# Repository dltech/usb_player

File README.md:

# usb_player
simple USB SD mp3 player based on stm32 MCU\
TODO:\
schematic (OK)\
board\
register defs (OK)\
RCC (OK)\
I2S PCM1754 sound out\
lm4811 power regul (OK)\
ADC sound in\
SDIO\
FAT32\
MP3 decoder\
SPI\
CC1101 4FSK\
speex build\
OTG FS USB FLASH (sd adapter)\
OTG FS USB FLASH FAT32 HOST\
STM32 DAC sound output

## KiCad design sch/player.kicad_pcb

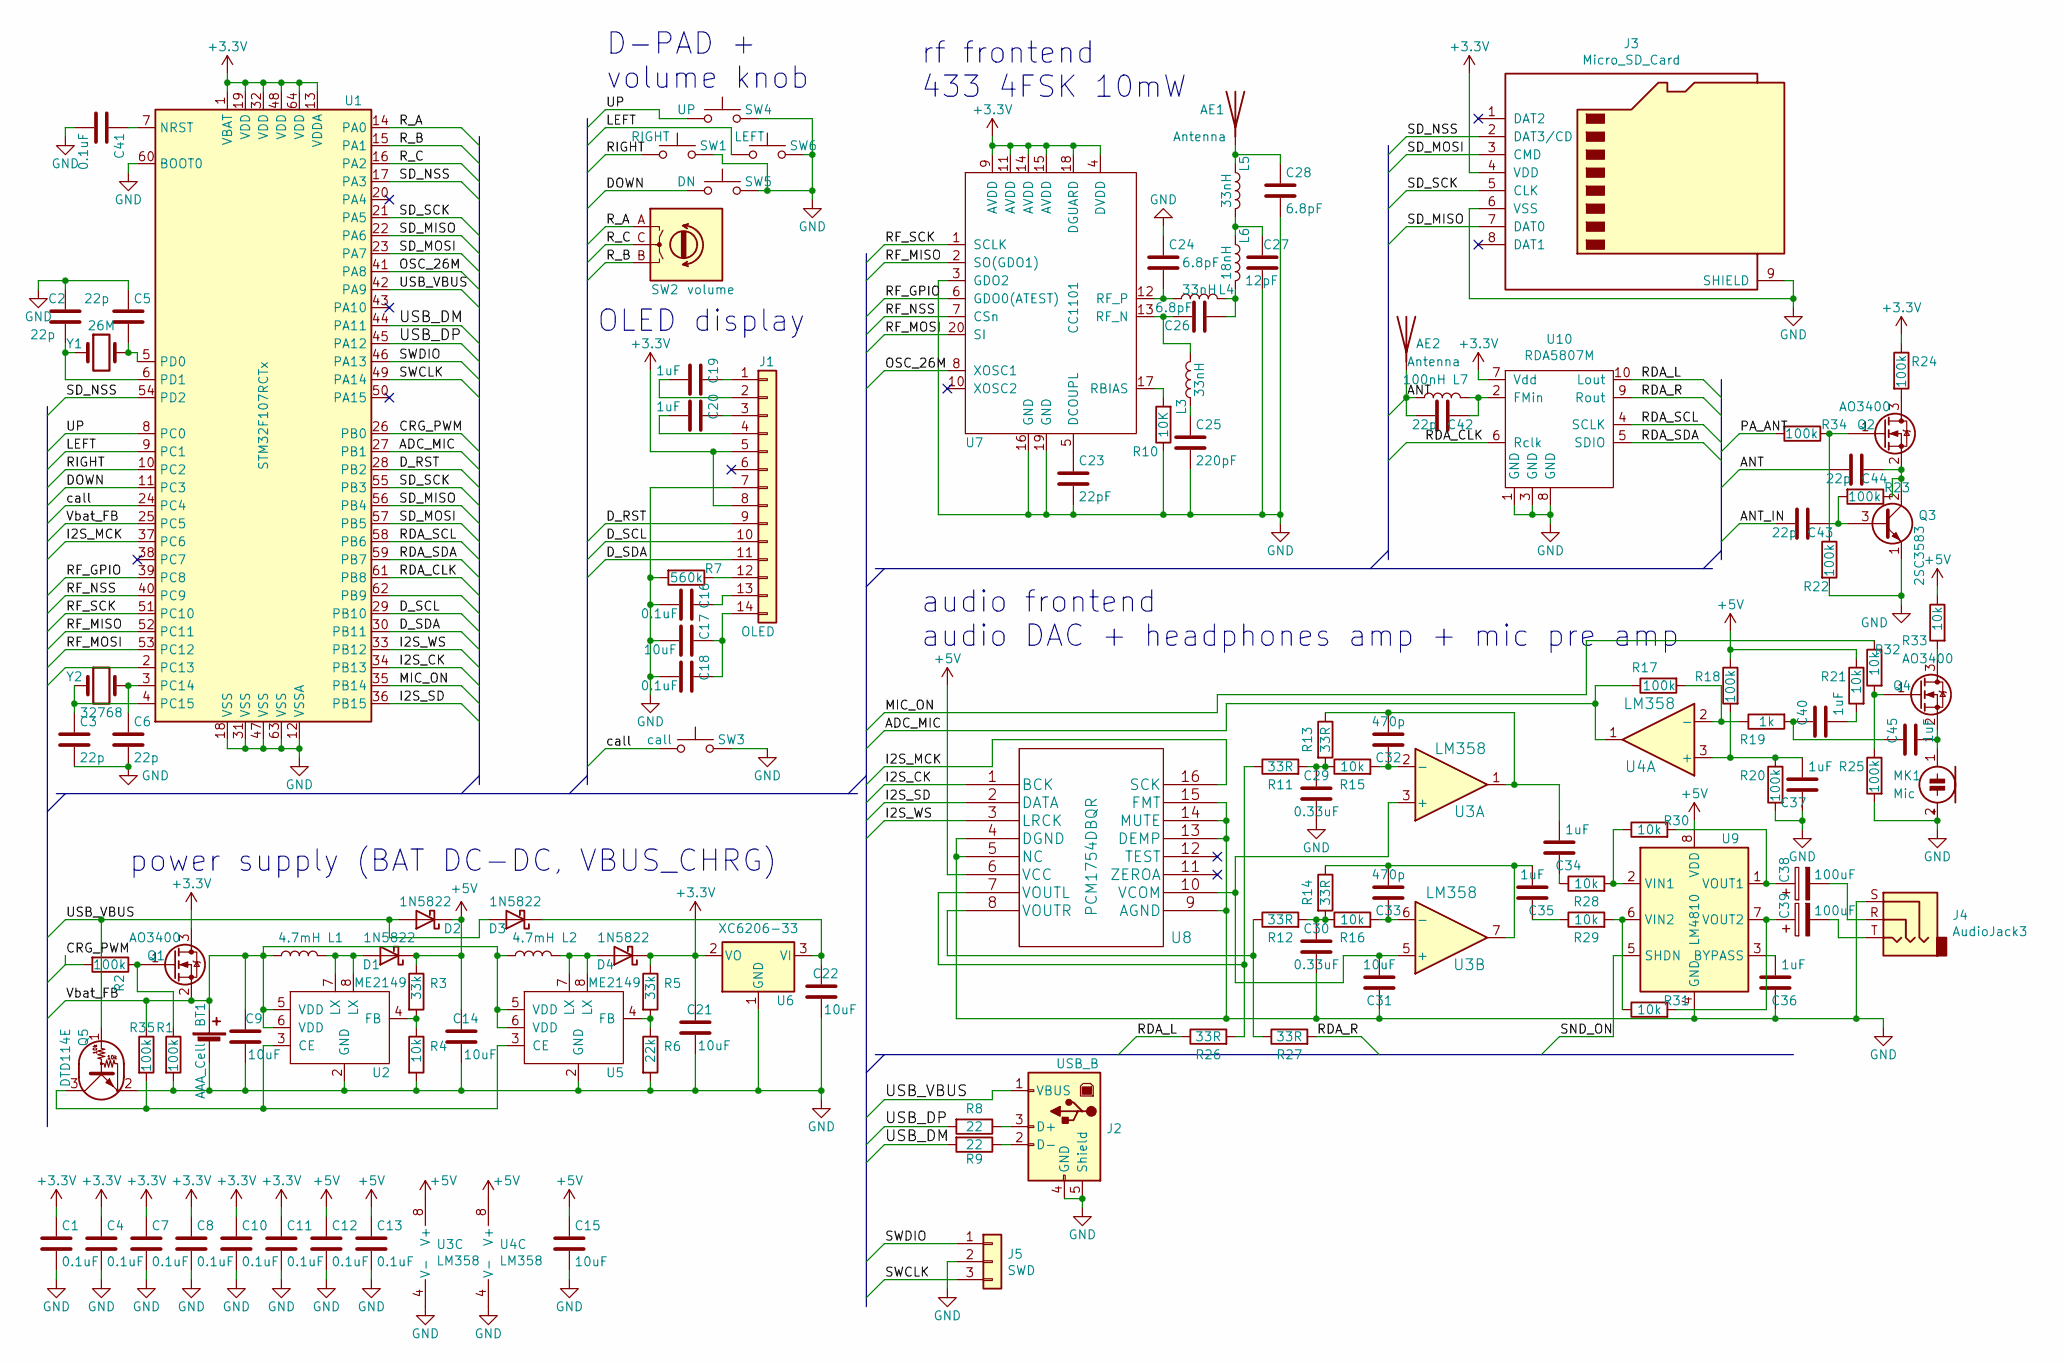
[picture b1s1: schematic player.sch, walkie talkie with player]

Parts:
AE1, AE2: Antenna; SolderWirePad_1x01_SMD_1x2mm
BT1: AAA_Cell; PinHeader_2x01_P2.54mm_Vertical
C1, C4, C7, C8, C10, C11, C12, C13, C16, C18, C41: 0.1uF; C_0402_1005Metric
C2, C3, C5, C6, C42, C43, C44: 22p; C_0402_1005Metric
C9, C14, C15, C17, C21, C22, C31: 10uF; C_0805_2012Metric
C19, C20, C34, C35, C36, C37, C40, C45: 1uF; C_0805_2012Metric
C23: 22pF; C_0402_1005Metric
C24, C26, C28: 6.8pF; C_0603_1608Metric
C25: 220pF; C_0603_1608Metric
C27: 12pF; C_0603_1608Metric
C29, C30: 0.33uF; C_0603_1608Metric
C32, C33: 470p; C_0603_1608Metric
C38, C39: 100uF; C_1206_3216Metric
D1, D2, D3, D4: 1N5822; D_SMA
J1: OLED; display_14p
J2: USB_B; USB_Micro-B_Molex_47346-0001
J3: Micro_SD_Card; microSD_HC_Hirose_DM3BT-DSF-PEJS
J4: AudioJack3; uefang
J5: SWD; 3WIRE_PADS
L1: 4.7mH; L_7.3x7.3_H4.5
L2: 4.7mH; L_1206_3216Metric
L3, L4, L5: 33nH; L_0603_1608Metric
L6: 18nH; L_0603_1608Metric
L7: 100nH; L_0603_1608Metric
MK1: Mic; CP_Radial_D5.0mm_P2.50mm
Q1, Q2, Q4: AO3400; SOT-23
Q3: 2SC3583; SOT-23
Q5: DTD114E; SOT-23
R1, R2, R20, R22, R23, R24, R25, R34, R35: 100k; R_0402_1005Metric
R3, R5: 33k; R_0805_2012Metric
R4, R15, R16, R21, R28, R29, R30, R31, R32, R33: 10k; R_0402_1005Metric
R6: 22k; R_0805_2012Metric
R7: 560k; R_0805_2012Metric
R8, R9: 22; R_0402_1005Metric
R10: 10K; R_0402_1005Metric
R11, R12, R13, R14, R26, R27: 33R; R_0402_1005Metric
R17, R18: 100k; C_0402_1005Metric
R19: 1k; R_0805_2012Metric
SW1: RIGHT; SW_PUSH_6mm
SW2: volume; mouse_encoder
SW3: call; SW_PUSH_6mm
SW4: UP; SW_PUSH_6mm
SW5: DN; SW_PUSH_6mm
SW6: LEFT; SW_PUSH_6mm
U1: STM32F107RCTx; LQFP-64_10x10mm_P0.5mm
U2, U5: ME2149; SSOP-8_3.9x5.05mm_P1.27mm
U3, U4: LM358; SSOP-8_3.9x5.05mm_P1.27mm
U6: XC6206-33; SOT-23
U7: CC1101; cc1101
U8: PCM1754DBQR; SSOP-16_3.9x4.9mm_P0.635mm
U9: LM4810; TSSOP-8_3x3mm_P0.65mm
U10: RDA5807M; MSOP-10_3x3mm_P0.5mm
Y1: 26M; Crystal_SMD_5032-2Pin_5.0x3.2mm
Y2: 32768; Crystal_SMD_2012-2Pin_2.0x1.2mm

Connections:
+5V: C12.1, C13.1, C14.2, C15.1, D1.1 (K), D2.1 (K), R3.1, R18.1, R21.1, R33.1, U3.8 (V+), U4.8 (V+), U8.6 (VCC), U9.8 (VDD)
/ADC_MIC: R17.1, U1.27 (PB1), U4.1
/ANT: AE2.1, C42.1, C44.1, L7.1
/ANT_IN: C43.1
/CRG_PWM: R2.2, U1.26 (PB0)
/DOWN: SW5.1, U1.11 (PC3)
/D_RST: J1.9, U1.28 (PB2)
/D_SCL: J1.10, U1.29 (PB10)
/D_SDA: J1.11, U1.30 (PB11)
/I2S_CK: U1.34 (PB13), U8.1 (BCK)
/I2S_MCK: U1.37 (PC6), U8.16 (SCK)
/I2S_SD: U1.36 (PB15), U8.2 (DATA)
/I2S_WS: U1.33 (PB12), U8.3 (LRCK)
/LEFT: SW6.1, U1.9 (PC1)
/MIC_ON: R32.1, U1.35 (PB14)
/OSC_26M: U1.41 (PA8), U7.8 (XOSC1)
/PA_ANT: R34.2
/RDA_CLK: U1.61 (PB8), U10.6 (Rclk)
/RDA_L: R26.1, U10.10 (Lout)
/RDA_R: R27.2, U10.9 (Rout)
/RDA_SCL: U1.58 (PB6), U10.4 (SCLK)
/RDA_SDA: U1.59 (PB7), U10.5 (SDIO)
/RF_GPIO: U1.39 (PC8), U7.6 (GDO0(ATEST))
/RF_MISO: U1.52 (PC11), U7.2 (SO(GDO1))
/RF_MOSI: U1.53 (PC12), U7.20 (SI)
/RF_NSS: U1.40 (PC9), U7.7 (CSn)
/RF_SCK: U1.51 (PC10), U7.1 (SCLK)
/RIGHT: SW1.1, U1.10 (PC2)
/R_A: SW2.A, U1.14 (PA0)
/R_B: SW2.B, U1.15 (PA1)
/R_C: SW2.C, U1.16 (PA2)
/SD_MISO: J3.7 (DAT0), U1.22 (PA6), U1.56 (PB4)
/SD_MOSI: J3.3 (CMD), U1.23 (PA7), U1.57 (PB5)
/SD_NSS: J3.2 (DAT3/CD), U1.17 (PA3), U1.54 (PD2)
/SD_SCK: J3.5 (CLK), U1.21 (PA5), U1.55 (PB3)
/SND_ON: U9.5 (SHDN)
/SWCLK: J5.3, U1.49 (PA14)
/SWDIO: J5.1, U1.46 (PA13)
/UP: SW4.1, U1.8 (PC0)
/USB_DM: R9.2, U1.44 (PA11)
/USB_DP: R8.2, U1.45 (PA12)
/USB_VBUS: D2.2 (A), D3.2 (A), J2.1 (VBUS), Q5.1 (B), U1.42 (PA9)
/Vbat_FB: BT1.1 (+), C9.2, L1.1, L2.1, Q1.2 (S), R35.1, U1.25 (PC5), U2.5 (VDD), U2.6 (VDD), U5.5 (VDD), U5.6 (VDD)
/call: SW3.1, U1.24 (PC4)
GND: BT1.2 (-), C1.2, C2.1, C3.2, C4.2, C5.1, C6.2, C7.2, C8.2, C9.1, C10.2, C11.2, C12.2, C13.2, C14.1, C15.2, C16.2, C17.1, C18.2, C21.1, C22.1, C23.2, C24.1, C25.2, C27.2, C28.2, C29.1, C30.1, C31.1, C36.1, C37.1, C41.2, J1.7, J2.4 (GND), J2.5 (Shield), J3.6 (VSS), J3.9 (SHIELD), J4.S, J5.2, MK1.2 (+), Q3.1 (E), Q5.2 (E), R1.2, R4.2, R6.2, R7.2, R10.1, R20.2, R22.2, R25.2, SW1.2, SW3.2, SW4.2, SW5.2, SW6.2, U1.12 (VSSA), U1.18 (VSS), U1.31 (VSS), U1.47 (VSS), U1.60 (BOOT0), U1.63 (VSS), U2.2 (GND), U3.4 (V-), U4.4 (V-), U5.2 (GND), U6.1 (GND), U7.3 (GDO2), U7.16 (GND), U7.19 (GND), U8.4 (DGND), U8.5 (NC), U8.9 (AGND), U8.13 (DEMP), U8.14 (MUTE), U8.15 (FMT), U9.4 (GND), U10.1 (GND), U10.3 (GND), U10.8 (GND)
unnamed: AE1.1, C28.1, L5.1
unnamed: C2.2, U1.6 (PD1), Y1.1
unnamed: C3.1, U1.4 (PC15), Y2.1
unnamed: C5.2, U1.5 (PD0), Y1.2
unnamed: C6.1, U1.3 (PC14), Y2.2
unnamed: C16.1, J1.13
unnamed: C17.2, C18.1, J1.14
unnamed: C19.1, J1.1
unnamed: C19.2, J1.2
unnamed: C20.1, J1.3
unnamed: C20.2, J1.4
unnamed: C23.1, U7.5 (DCOUPL)
unnamed: C24.2, L4.1, U7.12 (RF_P)
unnamed: C25.1, L3.1
unnamed: C26.1, L4.2, L6.2
unnamed: C26.2, L3.2, U7.13 (RF_N)
unnamed: C27.1, L5.2, L6.1
unnamed: C29.2, R11.2, R13.2, R15.1
unnamed: C30.2, R12.2, R14.2, R16.1
unnamed: C31.2, U3.3 (+), U3.5 (+), U8.10 (VCOM)
unnamed: C32.1, R15.2, U3.2 (-)
unnamed: C32.2, C34.2, R13.1, U3.1
unnamed: C33.1, R16.2, U3.6 (-)
unnamed: C33.2, C35.2, R14.1, U3.7
unnamed: C34.1, R28.1
unnamed: C35.1, R29.1
unnamed: C36.2, U9.3 (BYPASS)
unnamed: C37.2, R18.2, R20.1, U4.3 (+)
unnamed: C38.1, R30.2, U9.1 (VOUT1)
unnamed: C38.2, J4.R
unnamed: C39.1, R31.2, U9.7 (VOUT2)
unnamed: C39.2, J4.T
unnamed: C40.1, C45.1, R19.2
unnamed: C40.2, R21.2
unnamed: C41.1, U1.7 (NRST)
unnamed: C42.2, L7.2, U10.2 (FMin)
unnamed: C43.2, Q3.3 (B), R23.2
unnamed: C44.2, Q2.2 (S), Q3.2 (C), R23.1
unnamed: C45.2, MK1.1 (-), Q4.2 (S)
unnamed: D1.2 (A), L1.2, U2.7 (LX), U2.8 (LX)
unnamed: D4.2 (A), L2.2, U5.7 (LX), U5.8 (LX)
unnamed: J1.12, R7.1
unnamed: J2.2 (D-), R9.1
unnamed: J2.3 (D+), R8.1
unnamed: Q1.1 (G), R1.1, R2.1
unnamed: Q2.1 (G), R22.1, R34.1
unnamed: Q2.3 (D), R24.2
unnamed: Q4.1 (G), R25.1, R32.2
unnamed: Q4.3 (D), R33.2
unnamed: Q5.3 (C), R35.2, U2.3 (CE), U5.3 (CE)
unnamed: R3.2, R4.1, U2.4 (FB)
unnamed: R5.2, R6.1, U5.4 (FB)
unnamed: R10.2, U7.17 (RBIAS)
unnamed: R11.1, R26.2, U8.7 (VOUTL)
unnamed: R12.1, R27.1, U8.8 (VOUTR)
unnamed: R17.2, R19.1, U4.2 (-)
unnamed: R28.2, R30.1, U9.2 (VIN1)
unnamed: R29.2, R31.1, U9.6 (VIN2)

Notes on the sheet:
rf frontend 433 4FSK 10mW
audio frontend audio DAC + headphones amp + mic pre amp
D-PAD + volume knob
OLED display
power supply (BAT DC-DC, VBUS_CHRG)

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
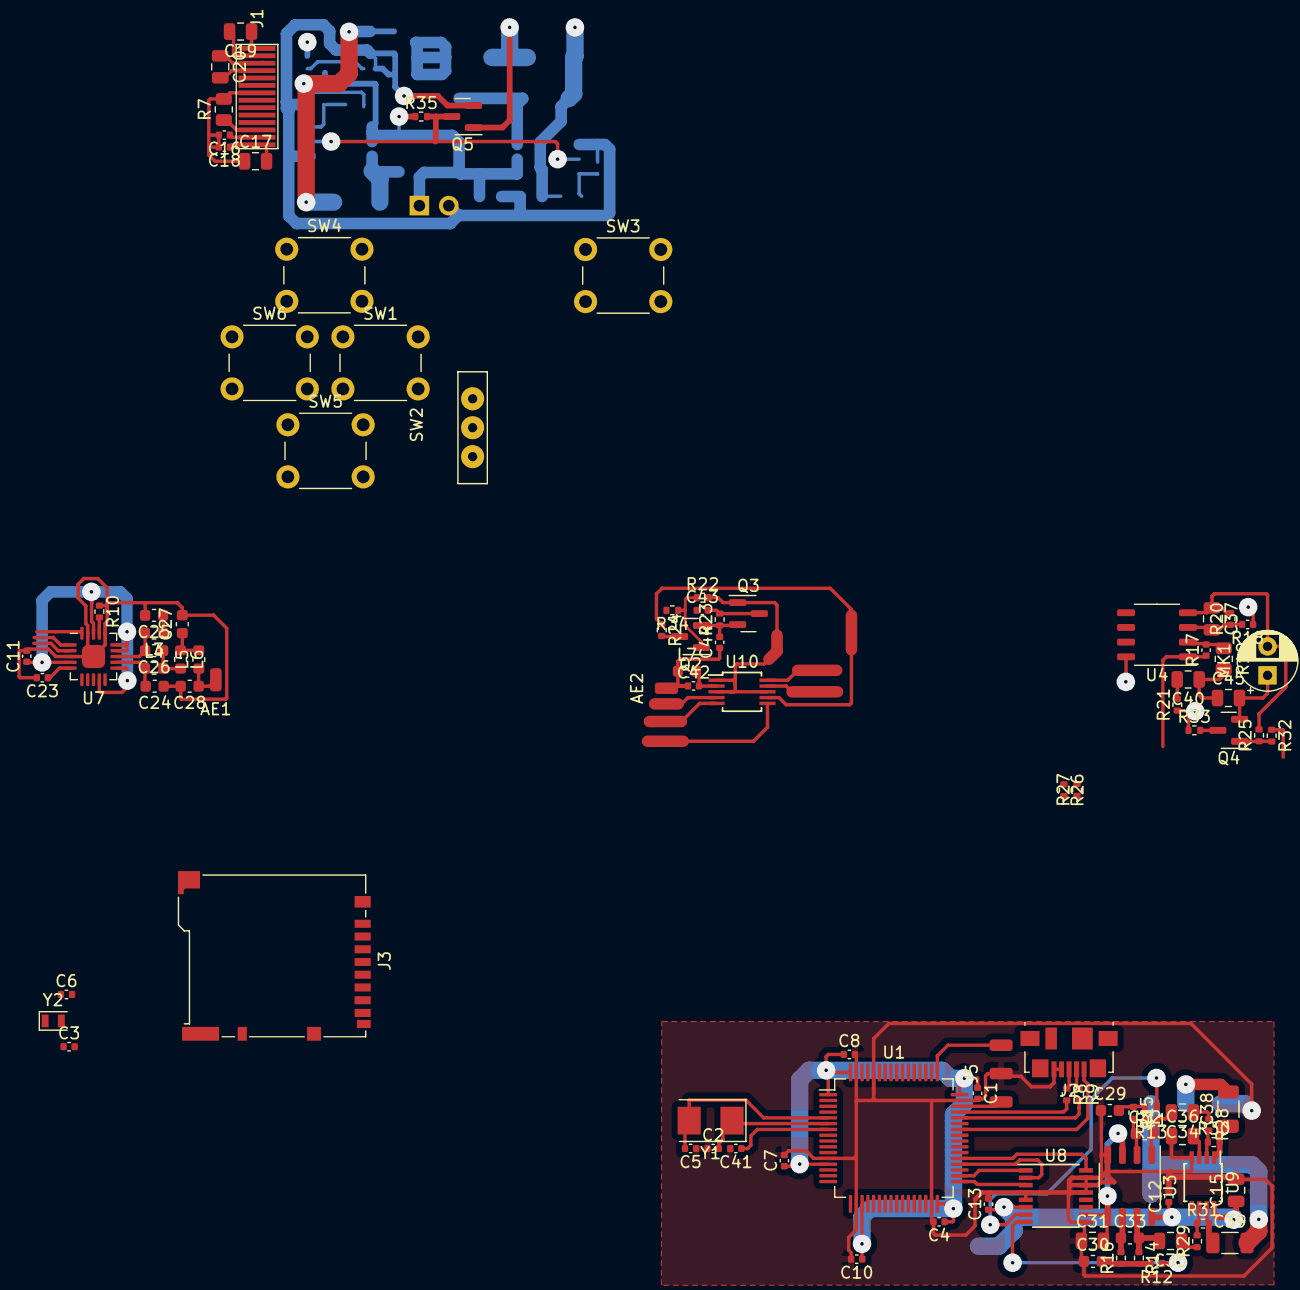
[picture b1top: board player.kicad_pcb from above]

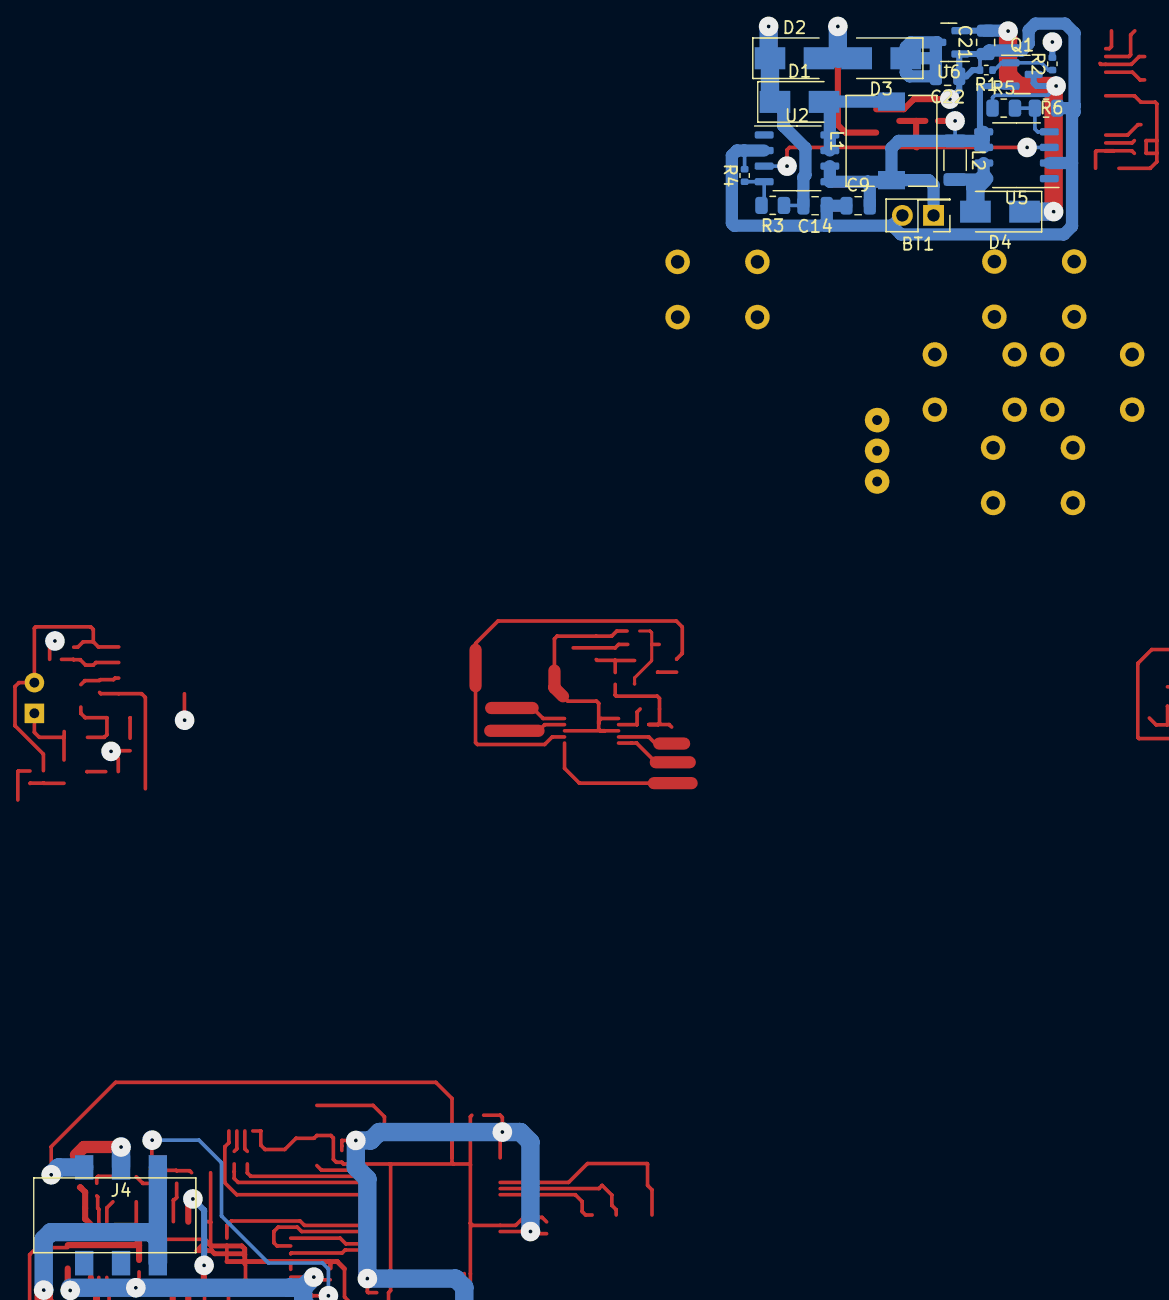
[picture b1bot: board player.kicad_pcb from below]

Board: 2 copper layers, 123 parts (22 on the bottom side), 102 nets.

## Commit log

2020-11-15 documentation is received
2021-09-27 create scenario
2021-10-14 rm libopencm3, add cmsis
2021-10-14 datasheets
2021-10-14 template for stm32f107
2021-10-14 rcc regs and configure ok
2021-10-14 sdio regs
2021-10-15 spi/i2s registers
2021-10-15 otgfs regs
2021-10-15 i2c regs
2021-10-23 adc and dac regs
2021-10-23 dma regs, for player all regs complete
2021-10-25 1101 regs added
2021-10-31 add pdf
2021-12-06 config 1101, almost
2021-12-06 pre built script for calc of 1101 freq
2021-12-22 schematic add
2021-12-22 freq calc verified with SmartRF
2021-12-23 mic add, rf433
2021-12-25 schematic almost complete
2021-12-26 footprints
2021-12-27 5807 FM sch add
2022-01-07 sch ok
2022-01-13 1101 strobe cmd
2022-04-14 rda registers
2022-04-23 add micro and audio checked
2022-04-24 soundcard test board
2022-05-02 sound front end scenario
